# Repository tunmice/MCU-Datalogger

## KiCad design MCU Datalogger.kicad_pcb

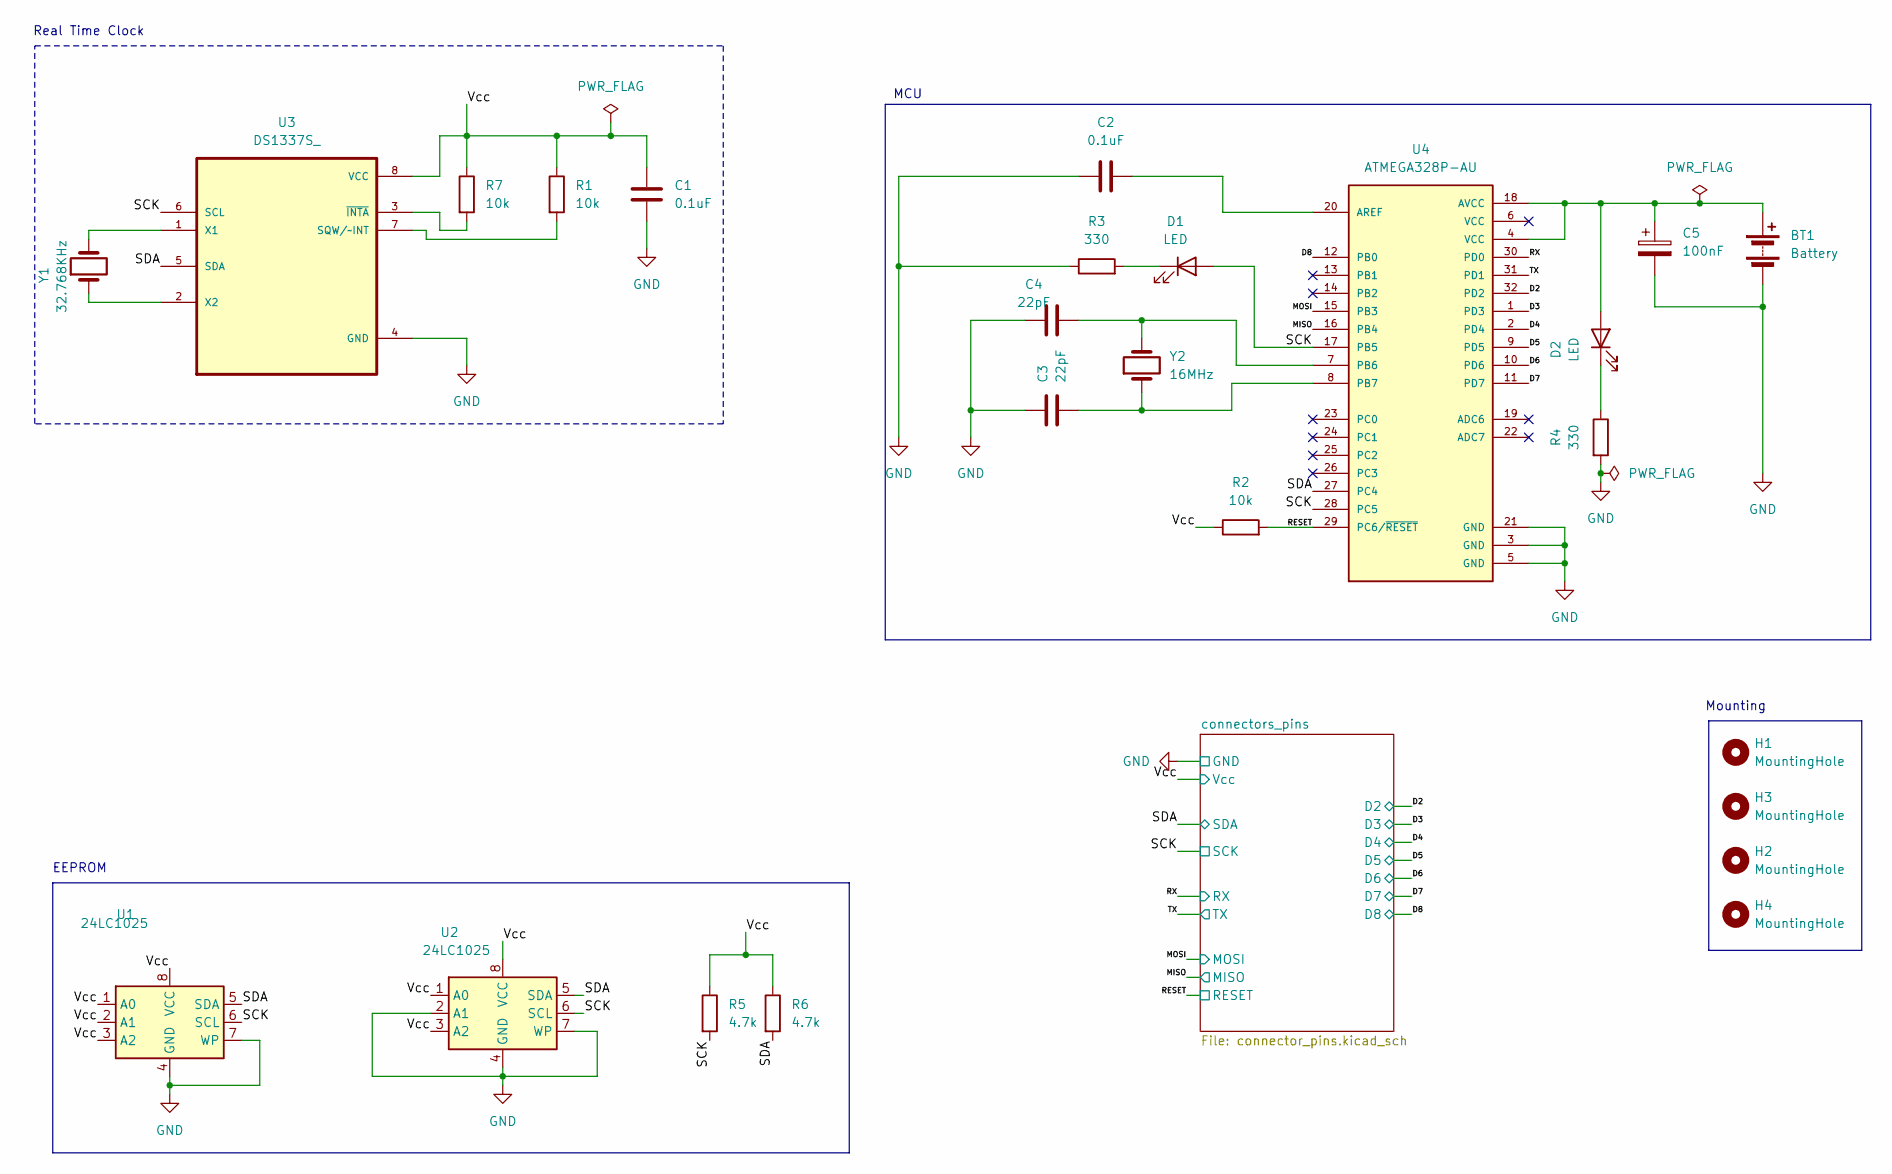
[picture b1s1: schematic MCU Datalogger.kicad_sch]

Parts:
BT1: Battery; PinHeader_1x02_P2.54mm_Vertical
C1, C2: 0.1uF; C_1206_3216Metric
C3, C4: 22pF; C_1206_3216Metric
C5: 100nF; C_1206_3216Metric
D1, D2: LED; LED_1206_3216Metric
H1, H2, H3, H4: MountingHole; MountingHole_2.1mm
R1, R2, R7: 10k; R_1206_3216Metric
R3, R4: 330; R_1206_3216Metric
R5, R6: 4.7k; R_1206_3216Metric
U1, U2: 24LC1025; SOIC-8_5.3x5.3mm_P1.27mm
U3: DS1337S_; SOIC127P600X175-8N
U4: ATMEGA328P-AU; QFP80P900X900X120-32N; PARTREV 8271A
Y1: 32.768KHz; Crystal_SMD_5032-2Pin_5.0x3.2mm_HandSoldering
Y2: 16MHz; Crystal_SMD_5032-2Pin_5.0x3.2mm_HandSoldering

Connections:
/D2: U4.32 (PD2); also elsewhere on the board
/D3: U4.1 (PD3); also elsewhere on the board
/D4: U4.2 (PD4); also elsewhere on the board
/D5: U4.9 (PD5); also elsewhere on the board
/D6: U4.10 (PD6); also elsewhere on the board
/D7: U4.11 (PD7); also elsewhere on the board
/D8: U4.12 (PB0); also elsewhere on the board
/MISO: U4.16 (PB4); also elsewhere on the board
/MOSI: U4.15 (PB3); also elsewhere on the board
/RESET: R2.2, U4.29 (PC6/~RESET); also elsewhere on the board
/RX: U4.30 (PD0); also elsewhere on the board
/SCK: D1.2 (A), R5.2, U1.6 (SCL), U2.6 (SCL), U3.6 (SCL), U4.17 (PB5), U4.28 (PC5); also elsewhere on the board
/SDA: R6.2, U1.5 (SDA), U2.5 (SDA), U3.5 (SDA), U4.27 (PC4); also elsewhere on the board
/TX: U4.31 (PD1); also elsewhere on the board
GND: BT1.2 (-), C1.2, C2.1, C3.1, C4.1, C5.2, R3.1, R4.2, U1.4 (GND), U1.7 (WP), U2.2 (A1), U2.4 (GND), U2.7 (WP), U3.4 (GND), U4.3 (GND), U4.5 (GND), U4.21 (GND); also elsewhere on the board
unnamed: D1.1 (K), R3.2
unnamed: D2.1 (K), R4.1
unnamed: R1.2, U3.7 (SQW/~INT)
unnamed: U3.1 (X1), Y1.2
unnamed: U3.2 (X2), Y1.1
unnamed: R7.2, U3.3 (~INTA)
unnamed: C2.2, U4.20 (AREF)
unnamed: C4.2, U4.7 (PB6), Y2.2
unnamed: C3.2, U4.8 (PB7), Y2.1

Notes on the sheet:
MCU
Real Time Clock
Mounting
EEPROM

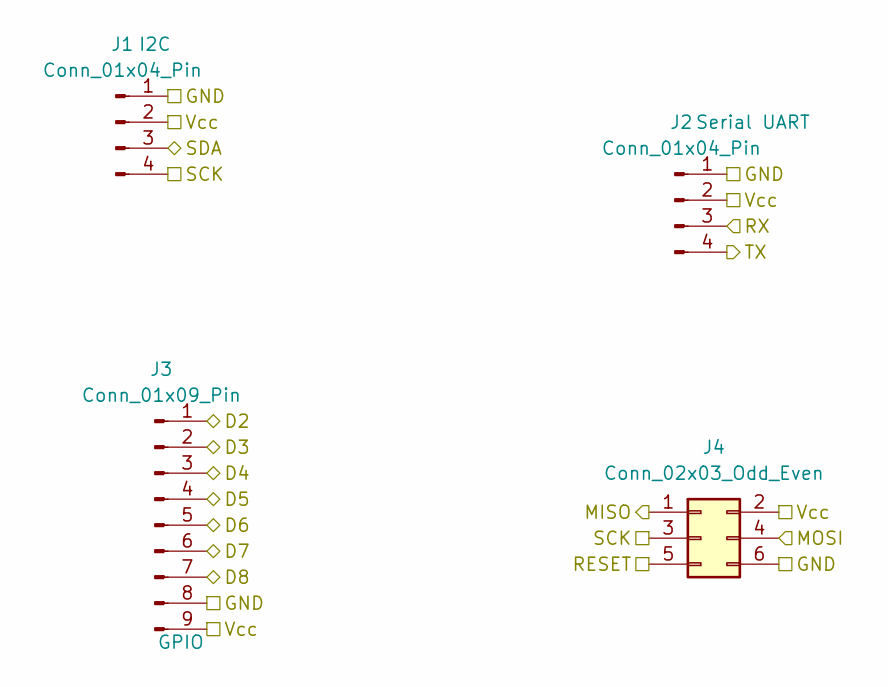
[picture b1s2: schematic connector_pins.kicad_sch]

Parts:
J1, J2: Conn_01x04_Pin; PinHeader_1x04_P2.54mm_Vertical
J3: Conn_01x09_Pin; PinHeader_1x09_P2.54mm_Vertical
J4: Conn_02x03_Odd_Even; PinHeader_2x03_P2.54mm_Vertical

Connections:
/D2: J3.1; also elsewhere on the board
/D3: J3.2; also elsewhere on the board
/D4: J3.3; also elsewhere on the board
/D5: J3.4; also elsewhere on the board
/D6: J3.5; also elsewhere on the board
/D7: J3.6; also elsewhere on the board
/D8: J3.7; also elsewhere on the board
/MISO: J4.1; also elsewhere on the board
/MOSI: J4.4; also elsewhere on the board
/RESET: J4.5; also elsewhere on the board
/RX: J2.3; also elsewhere on the board
/SCK: J1.4, J4.3; also elsewhere on the board
/SDA: J1.3; also elsewhere on the board
/TX: J2.4; also elsewhere on the board
GND: J1.1, J2.1, J3.8, J4.6; also elsewhere on the board

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
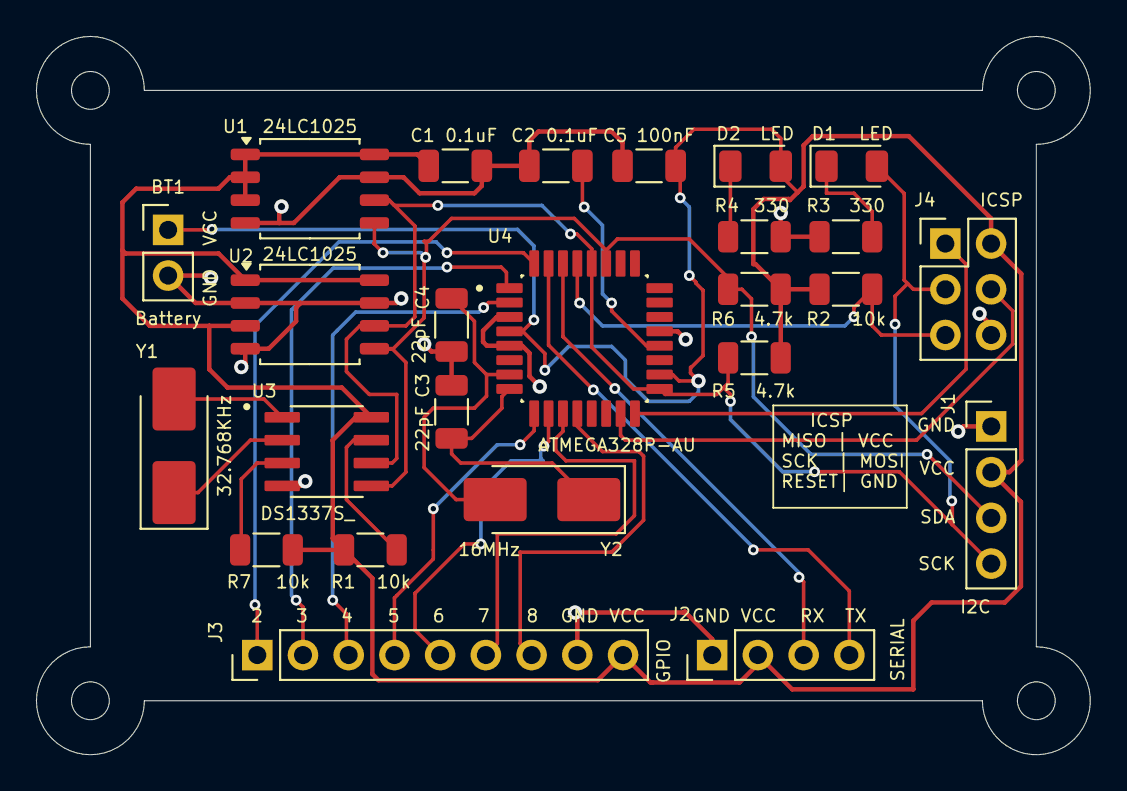
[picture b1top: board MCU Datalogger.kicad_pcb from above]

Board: 2 copper layers, 58.5 x 39.9 mm, 29 parts (0 on the bottom side), 25 nets.

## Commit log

2025-10-31 Git Setup for 2-layer PCB
2025-10-31 pcb layout setup
2025-10-31 complete layout of components
2025-10-31 drew proper shape of board & routed circuits partially
2025-10-31 routing done including copper fill
2025-10-31 silk screen labelling + routing + drc done
2025-11-01 Saved gerbers + completed project ish
